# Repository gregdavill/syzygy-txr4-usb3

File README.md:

# SYZYGY-TXR4-USB3 breakout

SYZYGY is an FPGA expansion standard for medium to high speed interfaces. Learn more and check out the specifications here: [https://syzygyfpga.io/](https://syzygyfpga.io/)

---

## What is it

A breakout to connect SYZYGYs 5Gbit serdes lanes through to a USB-C connector

Running the gateware luna stack on the FPGA can enumerate as a USB3 device.

## Folder structure

```
kicad-src: KiCad v6 source files
production:
 - Gerbers:      [project]_gerbers.zip
 - Schematic:    [project].pdf
 - Board render: [project].png
```

## Photo

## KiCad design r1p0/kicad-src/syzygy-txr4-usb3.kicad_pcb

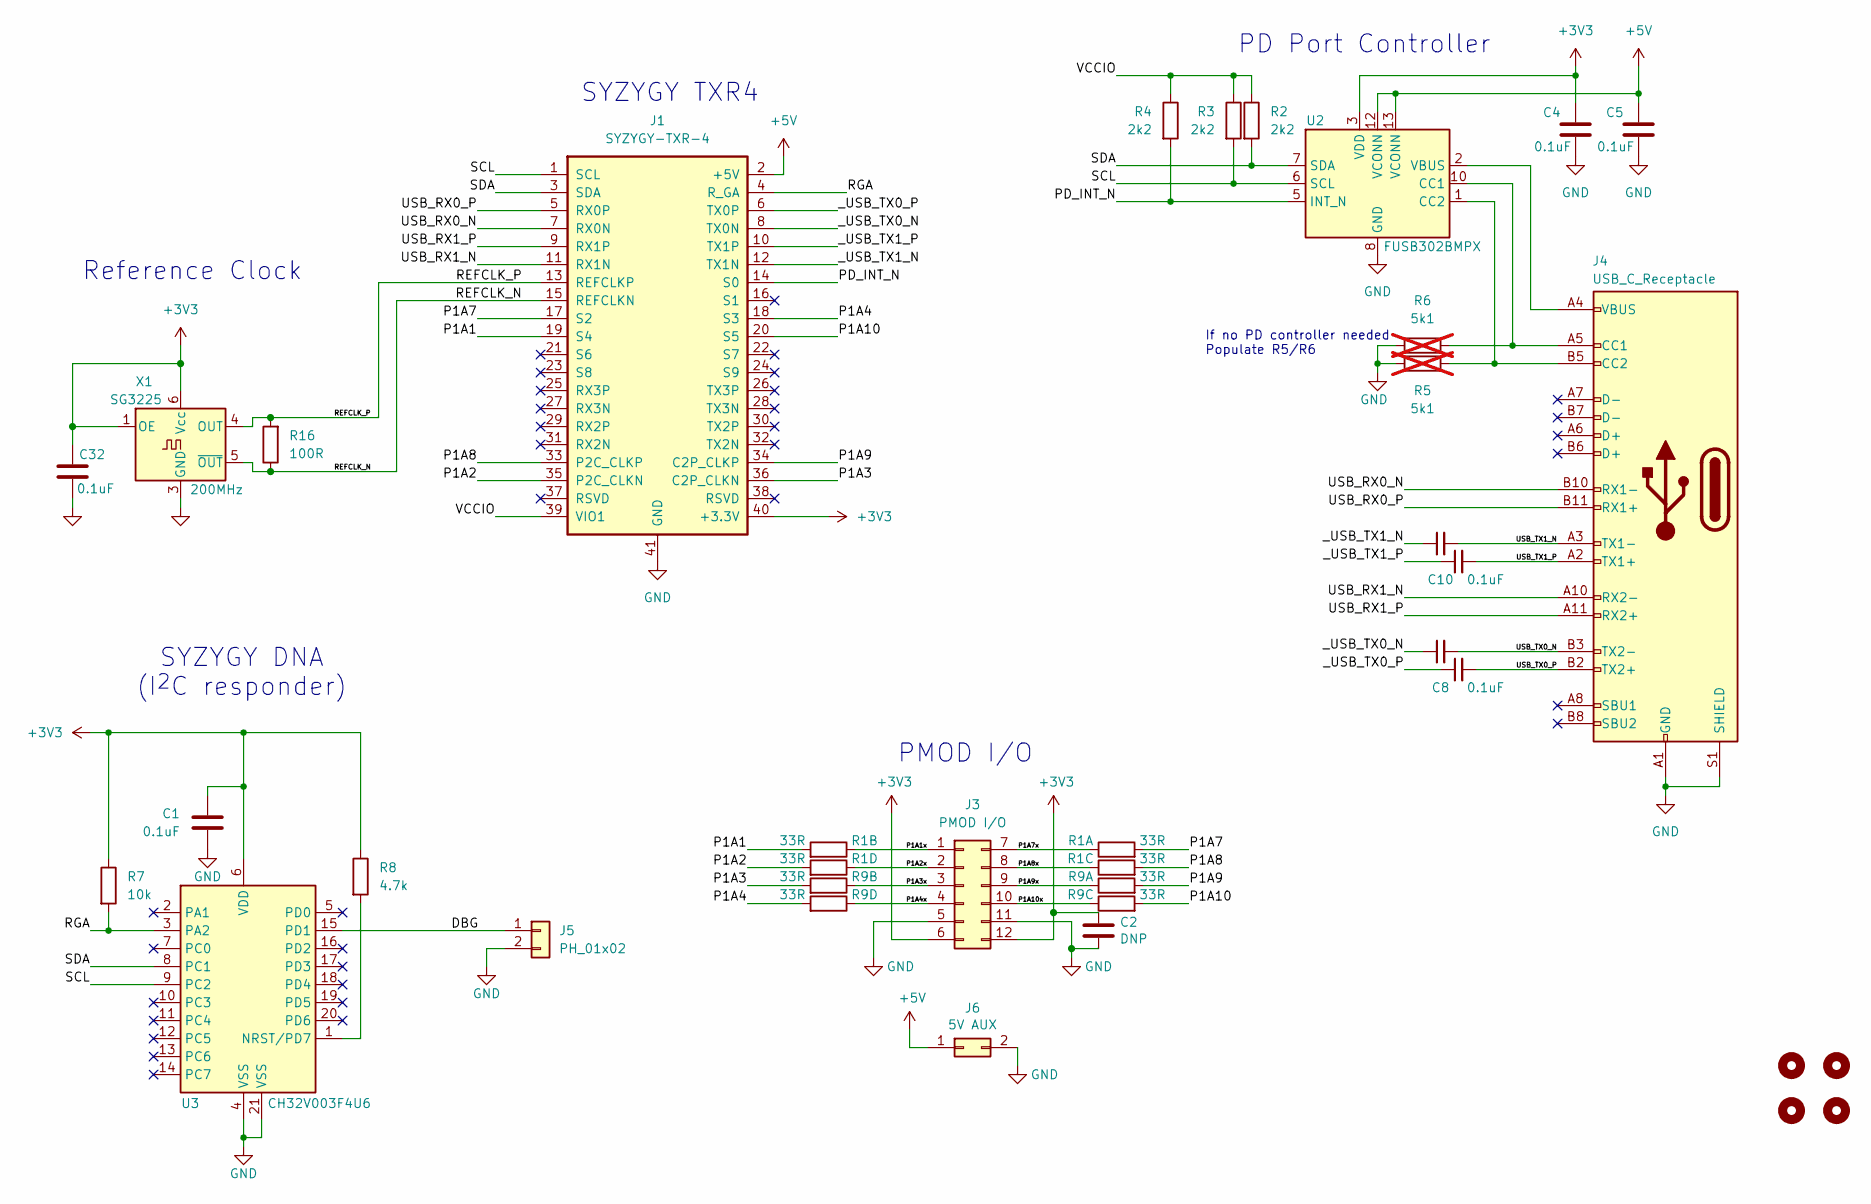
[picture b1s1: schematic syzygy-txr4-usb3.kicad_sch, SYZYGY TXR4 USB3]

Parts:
C1, C4, C5, C7, C8, C9, C10, C32: 0.1uF; C_0402_1005Metric
C2: DNP; C_0603_1608Metric
H1, H2, H3, H4: MountingHole; MountingHole_3.2mm_M3
J1: SYZYGY-TXR-4; SYZYGY-TXR-POD
J3: PMOD I/O; PinSocket_2x06_P2.54mm_Horizontal
J4: USB_C_Receptacle; USB_C_Receptacle_Amphenol_12401610E4-2A
J5: PH_01x02; PinHeader_1x02_P2.54mm_Vertical
J6: 5V AUX; PinHeader_2x01_P2.54mm_Vertical
R1, R9: 33R; R_Array_Convex_4x0402
R2, R3, R4: 2k2; R_0402_1005Metric
R5, R6: 5k1; R_0402_1005Metric; not fitted
R7: 10k; C_0402_1005Metric
R8: 4.7k; C_0402_1005Metric
R16: 100R; R_0402_1005Metric
U2: FUSB302BMPX; WQFN-14-1EP_2.5x2.5mm_P0.5mm_EP1.45x1.45mm
U3: CH32V003F4U6; QFN-20-1EP_3x3mm_P0.4mm_EP1.65x1.65mm_ThermalVias
X1: SG3225; Oscillator_SMD_Silicon_Labs_LGA-6_2.5x3.2mm_P1.25mm

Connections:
+3V3: C1.1, C2.2, C4.1, C32.1, J1.40 (+3.3V), J3.6, J3.12, R7.1, R8.1, U2.3 (VDD), U2.4 (VDD), U3.6 (VDD), X1.1 (OE), X1.6 (Vcc)
+5V: C5.1, J1.2 (+5V), J6.1, U2.12 (VCONN), U2.13 (VCONN)
/DBG: J5.1, U3.15 (PD1)
/P1A1: J1.19 (S4), R1.2
/P1A1x: J3.1, R1.7
/P1A2: J1.35 (P2C_CLKN), R1.4
/P1A2x: J3.2, R1.5
/P1A3: J1.36 (C2P_CLKN), R9.2
/P1A3x: J3.3, R9.7
/P1A4: J1.18 (S3), R9.4
/P1A4x: J3.4, R9.5
/P1A7: J1.17 (S2), R1.1
/P1A7x: J3.7, R1.8
/P1A8: J1.33 (P2C_CLKP), R1.3
/P1A8x: J3.8, R1.6
/P1A9: J1.34 (C2P_CLKP), R9.1
/P1A9x: J3.9, R9.8
/P1A10: J1.20 (S5), R9.3
/P1A10x: J3.10, R9.6
/PD_INT_N: J1.14 (S0), R4.2, U2.5 (INT_N)
/REFCLK_N: J1.15 (REFCLKN), R16.1, X1.5 (~OUT)
/REFCLK_P: J1.13 (REFCLKP), R16.2, X1.4 (OUT)
/RGA: J1.4 (R_GA), R7.2, U3.3 (PA2)
/SCL: J1.1 (SCL), R3.2, U2.6 (SCL), U3.9 (PC2)
/SDA: J1.3 (SDA), R2.2, U2.7 (SDA), U3.8 (PC1)
/USB_RX0_N: J1.7 (RX0N), J4.B10 (RX1-)
/USB_RX0_P: J1.5 (RX0P), J4.B11 (RX1+)
/USB_RX1_N: J1.11 (RX1N), J4.A10 (RX2-)
/USB_RX1_P: J1.9 (RX1P), J4.A11 (RX2+)
/USB_TX0_N: C7.2, J4.B3 (TX2-)
/USB_TX0_P: C8.2, J4.B2 (TX2+)
/USB_TX1_N: C9.2, J4.A3 (TX1-)
/USB_TX1_P: C10.2, J4.A2 (TX1+)
/VCCIO: J1.39 (VIO1), R2.1, R3.1, R4.1
/_USB_TX0_N: C7.1, J1.8 (TX0N)
/_USB_TX0_P: C8.1, J1.6 (TX0P)
/_USB_TX1_N: C9.1, J1.12 (TX1N)
/_USB_TX1_P: C10.1, J1.10 (TX1P)
GND: C1.2, C2.1, C4.2, C5.2, C32.2, J1.41 (GND), J3.5, J3.11, J4.A1 (GND), J4.A12 (GND), J4.B1 (GND), J4.B12 (GND), J4.S1 (SHIELD), J5.2, J6.2, R5.2, R6.2, U2.8 (GND), U2.9 (GND), U2.15 (GND), U3.4 (VSS), U3.21 (VSS), X1.3 (GND)
unnamed: J4.A5 (CC1), R6.1, U2.10 (CC1), U2.11 (CC1)
unnamed: J4.B5 (CC2), R5.1, U2.1 (CC2), U2.14 (CC2)
unnamed: J4.A4 (VBUS), J4.A9 (VBUS), J4.B4 (VBUS), J4.B9 (VBUS), U2.2 (VBUS)
unnamed: R8.2, U3.1 (NRST/PD7)

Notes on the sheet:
PMOD I/O
If no PD controller needed Populate R5/R6
SYZYGY DNA (I^{2}C responder)
SYZYGY TXR4
PD Port Controller
Reference Clock

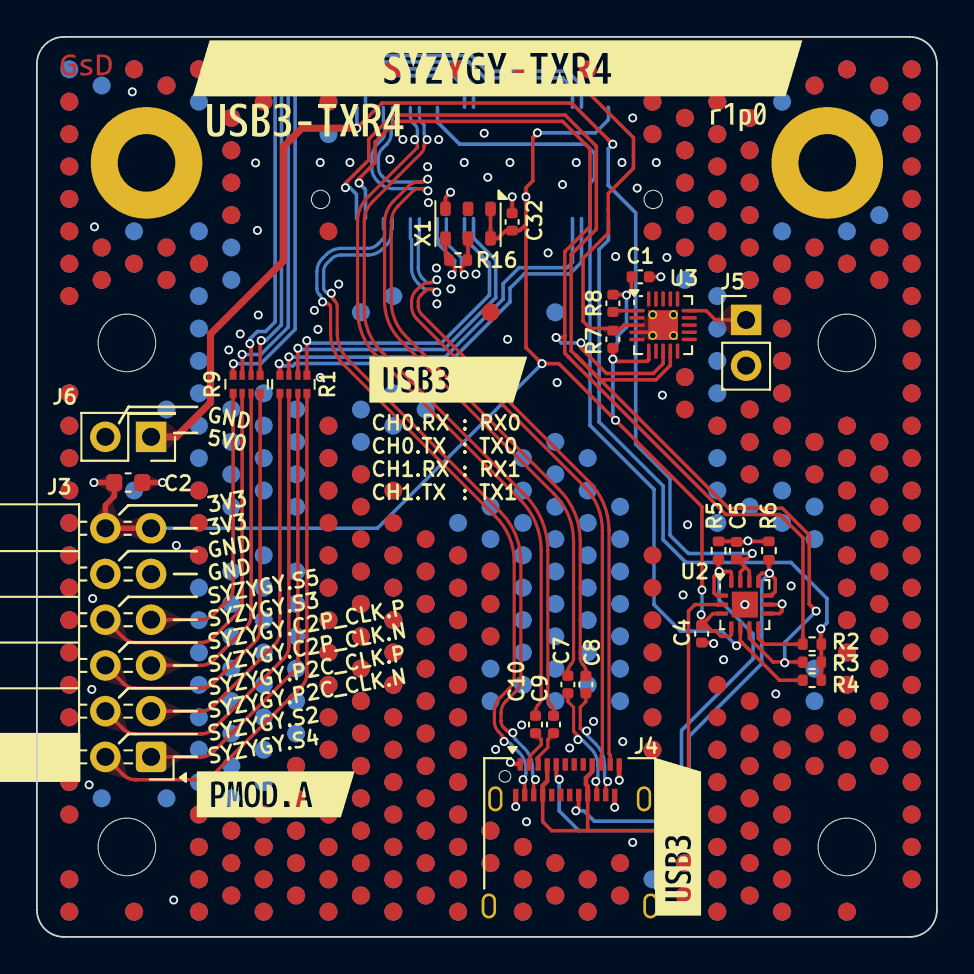
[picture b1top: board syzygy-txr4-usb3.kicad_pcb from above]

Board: 4 copper layers, 50.0 x 50.0 mm, 37 parts (1 on the bottom side), 43 nets.

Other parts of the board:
kibuzzard-66F7DAC0: G***; kibuzzard-66F7DAC0
kibuzzard-66F7DADB: G***; kibuzzard-66F7DADB
kibuzzard-66F7DBDF: G***; kibuzzard-66F7DBDF
kibuzzard-66F8E50F, kibuzzard-66F8E50F#2: G***; kibuzzard-66F8E50F
kibuzzard-66F8E506: G***; kibuzzard-66F8E506

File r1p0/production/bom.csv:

"Reference","Value","Datasheet","Footprint","Qty","DNP","Mfg","PN"
"C1,C4,C5,C7,C8,C9,C10,C32","0.1uF","~","Capacitor_SMD:C_0402_1005Metric","8","","Samsung Electro-Mechanics","CL05B104KA5NNNC"
"C2","DNP","","Capacitor_SMD:C_0603_1608Metric","1","","",""
"J1","SYZYGY-TXR-4","","gsd-footprints:SYZYGY-TXR-POD","1",""," Samtec Inc.","QTH-020-01-F-D-DP-A-K"
"J3","PMOD I/O","~","Connector_PinSocket_2.54mm:PinSocket_2x06_P2.54mm_Horizontal","1","","DEALON","DW254W-22-12-85"
"J4","USB_C_Receptacle","https://www.usb.org/sites/default/files/documents/usb_type-c.zip","Connector_USB:USB_C_Receptacle_Amphenol_12401610E4-2A","1","","Amphenol ICC","12401610E4#2A"
"J5","PH_01x02","~","Connector_PinHeader_2.54mm:PinHeader_1x02_P2.54mm_Vertical","1","","DEALON","DZ254R-11-02-63"
"J6","5V AUX","","Connector_PinHeader_2.54mm:PinHeader_2x01_P2.54mm_Vertical","1","","DEALON","DZ254R-11-02-63"
"R1,R9","33R","","Resistor_SMD:R_Array_Convex_4x0402","2","","Yageo"," YC124-JR-0733RL "
"R2,R3,R4","2k2","~","Resistor_SMD:R_0402_1005Metric","3","","Yageo","RC0402FR-072K2L"
"R5,R6","5k1","~","Resistor_SMD:R_0402_1005Metric","2","DNP","Yageo","RC0402FR-075K1L"
"R7","10k","~","Capacitor_SMD:C_0402_1005Metric","1","","Yageo","RC0402FR-0710KL"
"R8","4.7k","~","Capacitor_SMD:C_0402_1005Metric","1","","Yageo","RC0402FR-074K7L"
"R16","100R","~","Resistor_SMD:R_0402_1005Metric","1","","Yageo","AC0402FR-07100RL"
"U2","FUSB302BMPX","http://www.onsemi.com/pub/Collateral/FUSB302B-D.PDF","Package_DFN_QFN:WQFN-14-1EP_2.5x2.5mm_P0.5mm_EP1.45x1.45mm","1",""," onsemi","FUSB302BMPX"
"U3","CH32V003F4U6","http://www.wch-ic.com/downloads/CH32V003DS0_PDF.html","Package_DFN_QFN:QFN-20-1EP_3x3mm_P0.4mm_EP1.65x1.65mm_ThermalVias","1","","WCH(Jiangsu Qin Heng)","CH32V003F4U6"
"X1","SG3225","https://support.epson.biz/td/api/doc_check.php?dl=brief_SG5032VAN","Oscillator:Oscillator_SMD_Silicon_Labs_LGA-6_2.5x3.2mm_P1.25mm","1","","EPSON","SG3225VEN 125.000000M-CJGA3"

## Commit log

2026-05-16 Add r1p0 design files
2026-05-16 Add r1p1 design files
